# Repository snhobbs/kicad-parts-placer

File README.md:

# kicad-parts-placer
**Tool for precise, batch placement of components in a KiCad PCB layout.**

+ [Blog Post](https://maskset.net/kicad-parts-placer.html)

## Features
+ Exact batch placement of components in a layout
+ Groups the components allowing them to be moved and positioned as a group, easily ensuring exact alignment
+ Useful for:
  + Creating bed of nails tester
  + Positioning mechanically important parts
  + Maintaining a form factor across different designs
+ Similar in function to this [Altium feature](https://www.altium.com/documentation/altium-designer/pcb-cmd-placecomponentsfromfileplacecomponentsfromfile-ad)

## Example Use: Pogo pin & test pad placement
An example is provided at [example/example-placement](example/example-placement).
This example starts from a centroid file generated from an existing design, which is edited to serve as the input configuration:

A schematic is drawn up with matching reference designators:

The schematic is exported to a PCB which will look like this:

Running the script on this board with this command exports the following board with the components exactly aligned ready for layout. The group can be treated as a footprint, placed where ever is useful. During layout you only have to deal with a single coordinate as the position within the group is locked.

```{python}
kicad-parts-placer --pcb example-placement.kicad_pcb --config centroid-all-pos.csv --out example-placement_placed.kicad_pcb --drill_center
```

## Uses
    + Critical component placement: Exact placement of mounting holes, sensors, connectors, etc
    + Maintaining a form factor: Use the spreadsheet representation to either start a new project of a certain form factor or to ensure no parts have moved during layout
    + Reusing a bed-of-nails: Place the board outline and test pads the exact same way between versions to ensure the same jig can be used.
    
## Notes
+ Place parts in pcb layout from a configuration table.
+ Allows writing a config script which fully defines the parts
+ Connections are made either by updating from a schematic or passing a netlist
+ Use example of schematic to pcb placement
+ All parts are grouped together, locking their relative placement
+ Internal configuration is a dataframe with ref des, label/value, footprint, position x, position y. Notes fields can be added for documentation generation.
+ A separate config object can be that could pull in a board outline, stackup, etc describing the board.
+ Position, rotation, & ref des are available in the centroid file, that avoids requiring the source board be kicad.

## Installation
### PyPi
```
pip install kicad-parts-placer
```

### From Source
```
git clone https://github.com/snhobbs/kicad-parts-placer
cd kicad-parts-placer
pip install .
```

### KiCad Plugin
This tool is also available as a plugin via KiCad’s Plugin and Content Manager (PCM).

## References
+ [OpenFixture: Manual KiCad Location Export](https://tinylabs.io/openfixture-kicad-export)
+ [KiCad Schematic-to-PCB Position Plugin by Ian Ross](https://github.com/ian-ross/kicad-plugins)

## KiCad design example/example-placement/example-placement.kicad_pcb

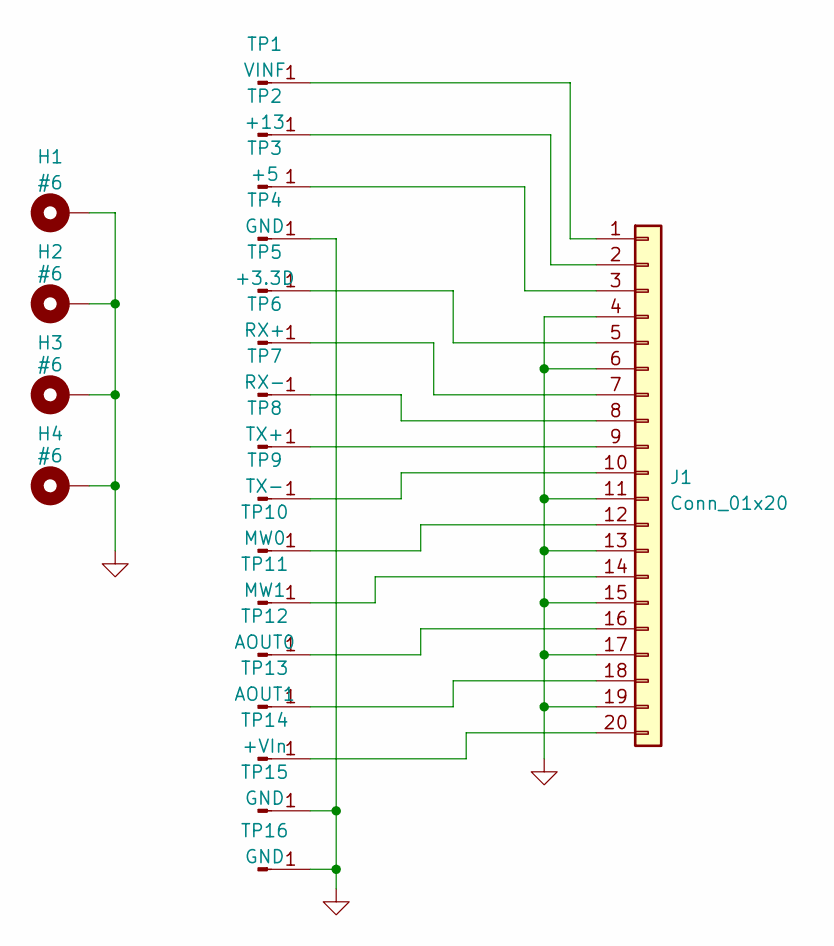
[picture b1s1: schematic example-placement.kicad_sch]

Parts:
H1, H2, H3, H4: #6; MountingHole_3.7mm_Pad_Via
J1: Conn_01x20; PinHeader_2x10_P2.54mm_Vertical_SMD
TP1: VINF; PinHeader_1x01_P2.54mm_Vertical
TP2: +13; PinHeader_1x01_P2.54mm_Vertical
TP3: +5; PinHeader_1x01_P2.54mm_Vertical
TP4, TP15, TP16: GND; PinHeader_1x01_P2.54mm_Vertical
TP5: +3.3D; PinHeader_1x01_P2.54mm_Vertical
TP6: RX+; PinHeader_1x01_P2.54mm_Vertical
TP7: RX-; PinHeader_1x01_P2.54mm_Vertical
TP8: TX+; PinHeader_1x01_P2.54mm_Vertical
TP9: TX-; PinHeader_1x01_P2.54mm_Vertical
TP10: MW0; PinHeader_1x01_P2.54mm_Vertical
TP11: MW1; PinHeader_1x01_P2.54mm_Vertical
TP12: AOUT0; PinHeader_1x01_P2.54mm_Vertical
TP13: AOUT1; PinHeader_1x01_P2.54mm_Vertical
TP14: +VIn; PinHeader_1x01_P2.54mm_Vertical

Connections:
GND: H1.1, H2.1, H3.1, H4.1, J1.4, J1.6, J1.11, J1.13, J1.15, J1.17, J1.19, TP4.1, TP15.1, TP16.1
unnamed: J1.1, TP1.1
unnamed: J1.2, TP2.1
unnamed: J1.3, TP3.1
unnamed: J1.5, TP5.1
unnamed: J1.7, TP6.1
unnamed: J1.8, TP7.1
unnamed: J1.9, TP8.1
unnamed: J1.10, TP9.1
unnamed: J1.12, TP10.1
unnamed: J1.14, TP11.1
unnamed: J1.16, TP12.1
unnamed: J1.18, TP13.1
unnamed: J1.20, TP14.1

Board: 2 copper layers, 21 parts (0 on the bottom side), 14 nets, no tracks yet.

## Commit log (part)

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2022-11-17 Adding references
2022-11-17 Adding use cases
2022-11-19 removing board centering
2022-11-19 adding example
2022-11-19 adding make for example
2022-11-19 adding setup
2022-11-19 adding build
2022-11-19 adding example images
2022-11-19 updating readme with images
2022-11-19 updating requirements
2022-11-19 fix spelling
2022-11-21 Update README.md
    Adding reference to TestPointReport2STL
2023-02-23 updating requirements
    fix spelling
    fix spelling
    updates for kicad 7.0.0
    Update requirements.txt
    Update README.md
    Adding reference to TestPointReport2STL
2023-03-09 adding example placement
2023-11-17 adding flip option
2023-12-05 moving to cookiecutter project
2023-12-05 Bump version: 0.1.0 → 0.1.1
2023-12-19 Bump version: 0.1.1 → 0.1.2
2023-12-19 merging changes, updating examples
2023-12-19 linting
2023-12-19 Bump version: 0.1.2 → 0.1.3
2024-02-04 breaking functions out of cli for library use
2024-02-06 adding parts flipping
2024-02-12 adding parts placing short circuit
2024-05-14 repackaging, linting
2024-05-15 adding mypy, linting
2024-05-16 Bump version: 0.1.3 → 0.1.4
2024-05-16 release, fixing makefile build for pyproject.toml
2024-06-24 updating placement, adding aux origin
2024-06-24 Bump version: 0.1.4 → 0.1.5
2024-06-24 Update LICENSE
2024-06-24 fixing rotation order
2024-06-24 Bump version: 0.1.5 → 0.1.6
2024-06-24 adding file io and removing spreadsheet_wrangler
2024-06-24 Bump version: 0.1.6 → 0.1.7
2024-06-24 adding version
2024-06-24 using mirror in x as it's more natural
2024-07-07 fixed doc build
2024-07-16 updating build
2024-07-16 updates for plugin
2024-07-16 adding a couple hacks to work with plugin
2024-07-31 updating readme
2024-09-09 adding file_io tests
2024-09-09 adding click pylint options
2024-09-09 making pylint happy
2024-09-09 Bump version: 0.1.7 → 0.1.8
2024-09-10 removing numpy
2024-09-13 adding header pseudonyms
2024-09-13 removing pandas dependancy
2024-09-14 adding input checking
2024-09-14 Bump version: 0.1.8 → 0.1.9
2024-09-14 removed pcms dataframe
2024-09-14 moving dataframe checking out of parts-placer
2024-09-14 Bump version: 0.1.9 → 0.1.10
2024-09-14 adding checking for ref des
2024-09-14 Bump version: 0.1.10 → 0.1.11
2025-06-26 renaming constants to capitol
2025-06-26 fixing setting of a scalar behaviour
2025-07-09 moving board side to enums and adding extra checking
2026-04-01 adding version test gate
2026-04-08 refactoring to use a dataclass for the part description rows. Adding tests
2026-04-21 fixing typing
